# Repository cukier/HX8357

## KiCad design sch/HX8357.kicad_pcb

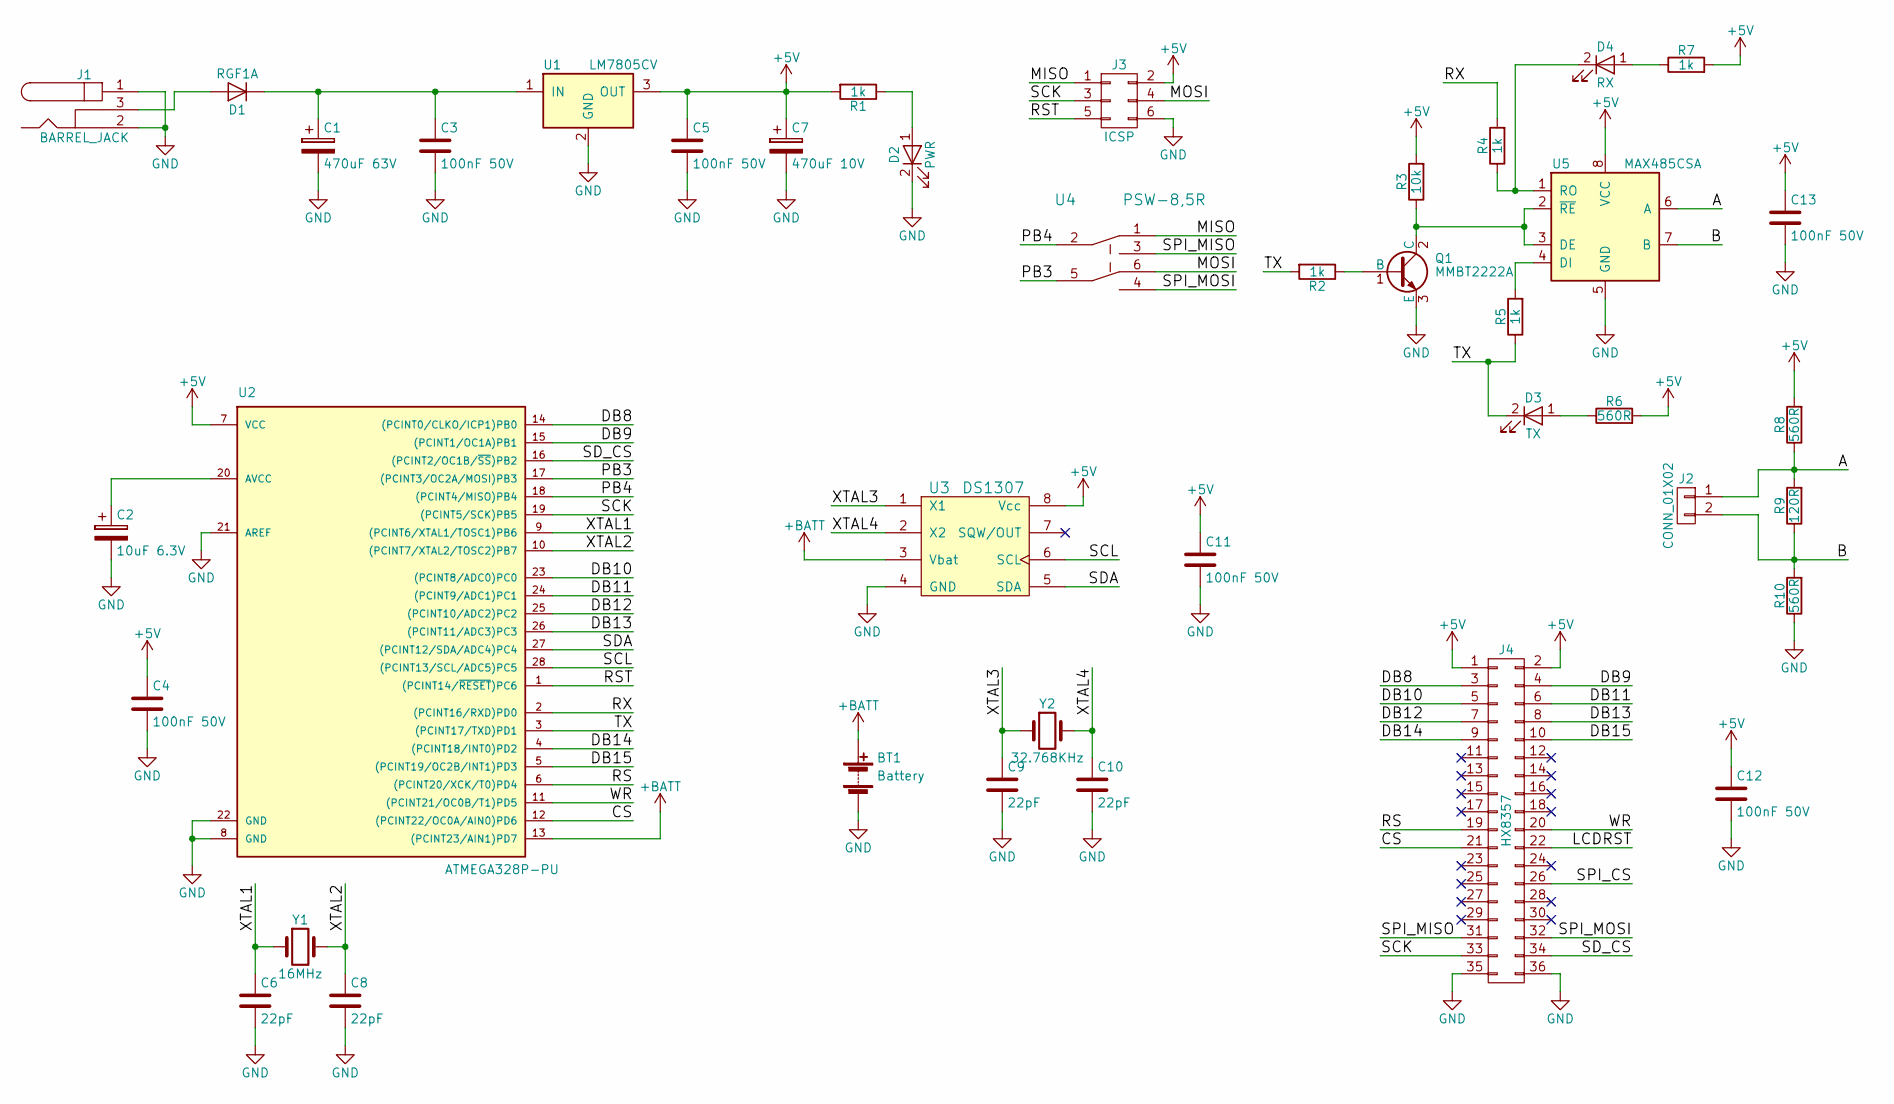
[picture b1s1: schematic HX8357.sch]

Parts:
BT1: Battery; keystone_103
C1: 470uF 63V; CP_12.5x25mm
C2: 10uF 6.3V; CP_4x5mm
C3, C4, C5, C11, C12, C13: 100nF 50V; c_0805
C6, C8, C9, C10: 22pF; c_0805
C7: 470uF 10V; CP_8x11.5mm
D1: RGF1A; do214ac
D2: PWR; Led_0805
D3: TX; Led_0805
D4: RX; Led_0805
J1: BARREL_JACK; dc_socket
J2: CONN_01X02; mkds_1,5-2
J3: ICSP; pin_strip_3x2
J4: HX8357; pin_strip_18x2
Q1: MMBT2222A; sot23
R1, R2, R4, R5, R7: 1k; r_0805
R3: 10k; r_0805
R6, R8, R10: 560R; r_0805
R9: 120R; r_0805
U1: LM7805CV; to220_5772
U2: ATMEGA328P-PU; dil_28-300_socket
U3: DS1307; so-8
U4: PSW-8,5R; psw-8,5
U5: MAX485CSA; so-8
Y1: 16MHz; crystal_hc-49%2fsmd
Y2: 32.768KHz; crystal_tc-26_horiz

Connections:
+5V: C4.1, C5.1, C7.1, C11.1, C12.1, C13.1, J3.2, J4.1, J4.2, R1.2, R3.2, R6.2, R7.2, R8.2, U1.3 (OUT), U2.7 (VCC), U3.8 (Vcc), U5.8 (VCC); also elsewhere on the board
+BATT: BT1.1 (+), U2.13 ((PCINT23/AIN1)PD7), U3.3 (Vbat)
/A: J2.1, R8.1, R9.2, U5.6 (A)
/B: J2.2, R9.1, R10.2, U5.7 (B)
/CS: J4.21, U2.12 ((PCINT22/OC0A/AIN0)PD6)
/DB8: J4.3, U2.14 ((PCINT0/CLKO/ICP1)PB0)
/DB9: J4.4, U2.15 ((PCINT1/OC1A)PB1)
/DB10: J4.5, U2.23 ((PCINT8/ADC0)PC0)
/DB11: J4.6, U2.24 ((PCINT9/ADC1)PC1)
/DB12: J4.7, U2.25 ((PCINT10/ADC2)PC2)
/DB13: J4.8, U2.26 ((PCINT11/ADC3)PC3)
/DB14: J4.9, U2.4 ((PCINT18/INT0)PD2)
/DB15: J4.10, U2.5 ((PCINT19/OC2B/INT1)PD3)
/LCDRST: J4.22
/MISO: J3.1, U4.1
/MOSI: J3.4, U4.6
/PB3: U2.17 ((PCINT3/OC2A/MOSI)PB3), U4.5
/PB4: U2.18 ((PCINT4/MISO)PB4), U4.2
/RS: J4.19, U2.6 ((PCINT20/XCK/T0)PD4)
/RST: J3.5, U2.1 ((PCINT14/~RESET~)PC6)
/RX: R4.2, U2.2 ((PCINT16/RXD)PD0)
/SCK: J3.3, J4.33, U2.19 ((PCINT5/SCK)PB5)
/SCL: U2.28 ((PCINT13/SCL/ADC5)PC5), U3.6 (SCL); also elsewhere on the board
/SDA: U2.27 ((PCINT12/SDA/ADC4)PC4), U3.5 (SDA); also elsewhere on the board
/SD_CS: J4.34, U2.16 ((PCINT2/OC1B/~SS~)PB2)
/SPI_CS: J4.26
/SPI_MISO: J4.31, U4.3
/SPI_MOSI: J4.32, U4.4
/TX: D3.2 (K), R2.2, R5.1, U2.3 ((PCINT17/TXD)PD1)
/WR: J4.20, U2.11 ((PCINT21/OC0B/T1)PD5)
/XTAL1: C6.1, U2.9 ((PCINT6/XTAL1/TOSC1)PB6), Y1.1
/XTAL2: C8.1, U2.10 ((PCINT7/XTAL2/TOSC2)PB7), Y1.2
/XTAL3: C9.1, U3.1 (X1), Y2.1
/XTAL4: C10.1, U3.2 (X2), Y2.2
GND: BT1.2 (-), C1.2, C2.2, C3.2, C4.2, C5.2, C6.2, C7.2, C8.2, C9.2, C10.2, C11.2, C12.2, C13.2, D2.2 (K), J1.1, J1.2, J3.6, J4.35, J4.36, Q1.3 (E), R10.1, U1.2 (GND), U2.8 (GND), U2.21 (AREF), U2.22 (GND), U3.4 (GND), U5.5 (GND)
unnamed: C1.1, C3.1, D1.2 (K), U1.1 (IN)
unnamed: C2.1, U2.20 (AVCC)
unnamed: D1.1 (A), J1.3
unnamed: D2.1 (A), R1.1
unnamed: D3.1 (A), R6.1
unnamed: D4.1 (A), R7.1
unnamed: D4.2 (K), R4.1, U5.1 (RO)
unnamed: Q1.1 (B), R2.1
unnamed: Q1.2 (C), R3.1, U5.2 (~RE~), U5.3 (DE)
unnamed: R5.2, U5.4 (DI)

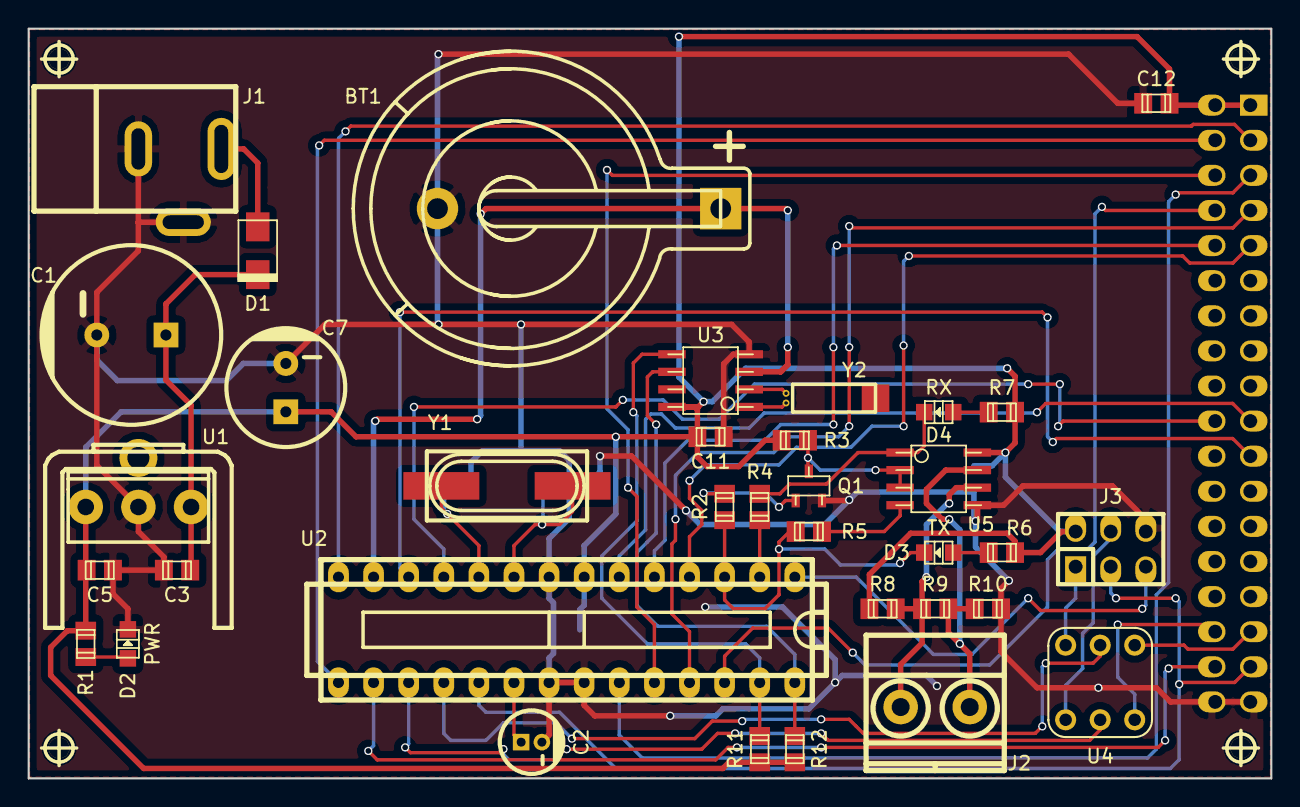
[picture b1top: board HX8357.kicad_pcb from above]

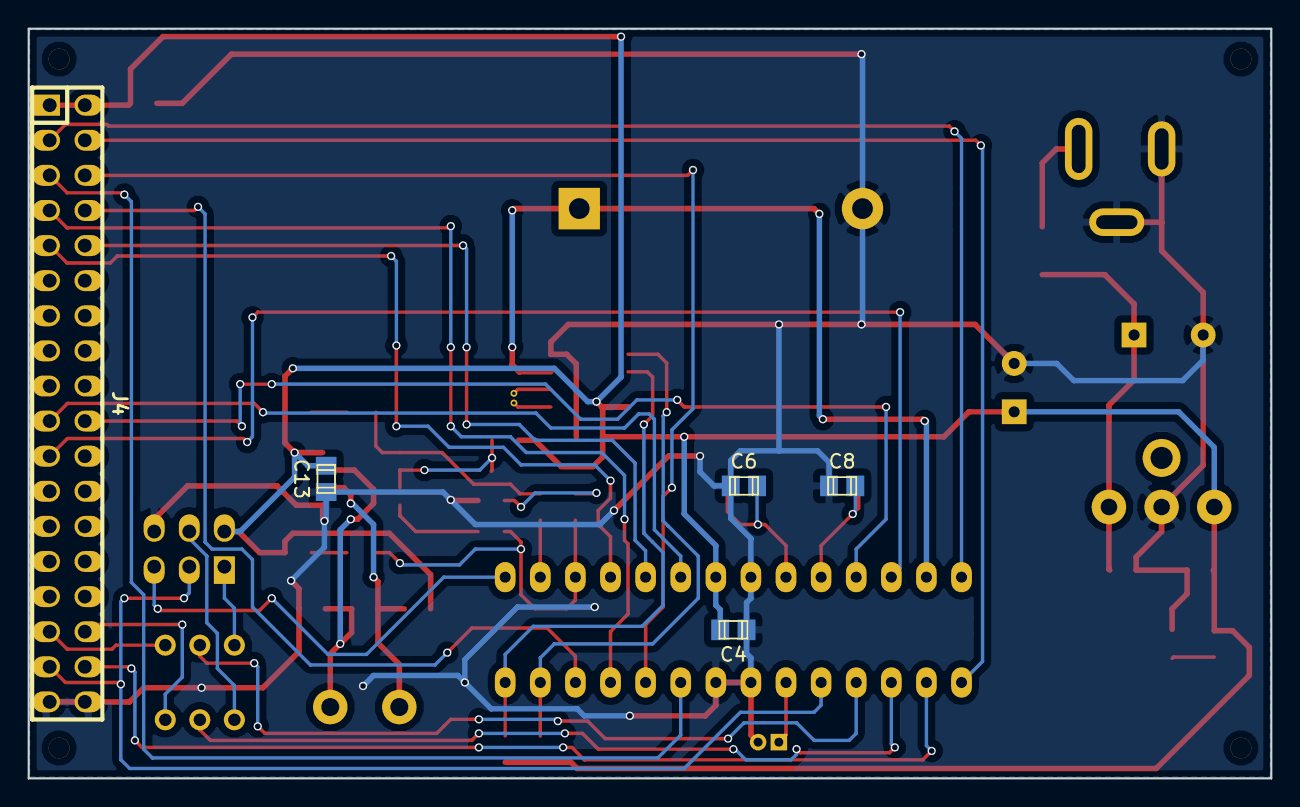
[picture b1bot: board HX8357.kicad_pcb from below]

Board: 2 copper layers, 89.9 x 54.2 mm, 44 parts (5 on the bottom side), 43 nets.

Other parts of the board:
R11, R12: 4k7; r_0805
hole_1mm5, hole_1mm5#2, hole_1mm5#3, hole_1mm5#4: VAL**; hole_1mm5

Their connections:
+5V: R11.2, R12.2; also elsewhere on the board
/SCL: R12.1; also elsewhere on the board
/SDA: R11.1; also elsewhere on the board

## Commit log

2017-06-20 documentos
2017-06-20 esquematico
2017-06-21 Placa
